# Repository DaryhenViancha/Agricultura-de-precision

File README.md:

# Control de Biosistemas
Proyecto de Sistemas Embebidos 2021-2.    
Para la documentación del proyecto revisar la wiki.

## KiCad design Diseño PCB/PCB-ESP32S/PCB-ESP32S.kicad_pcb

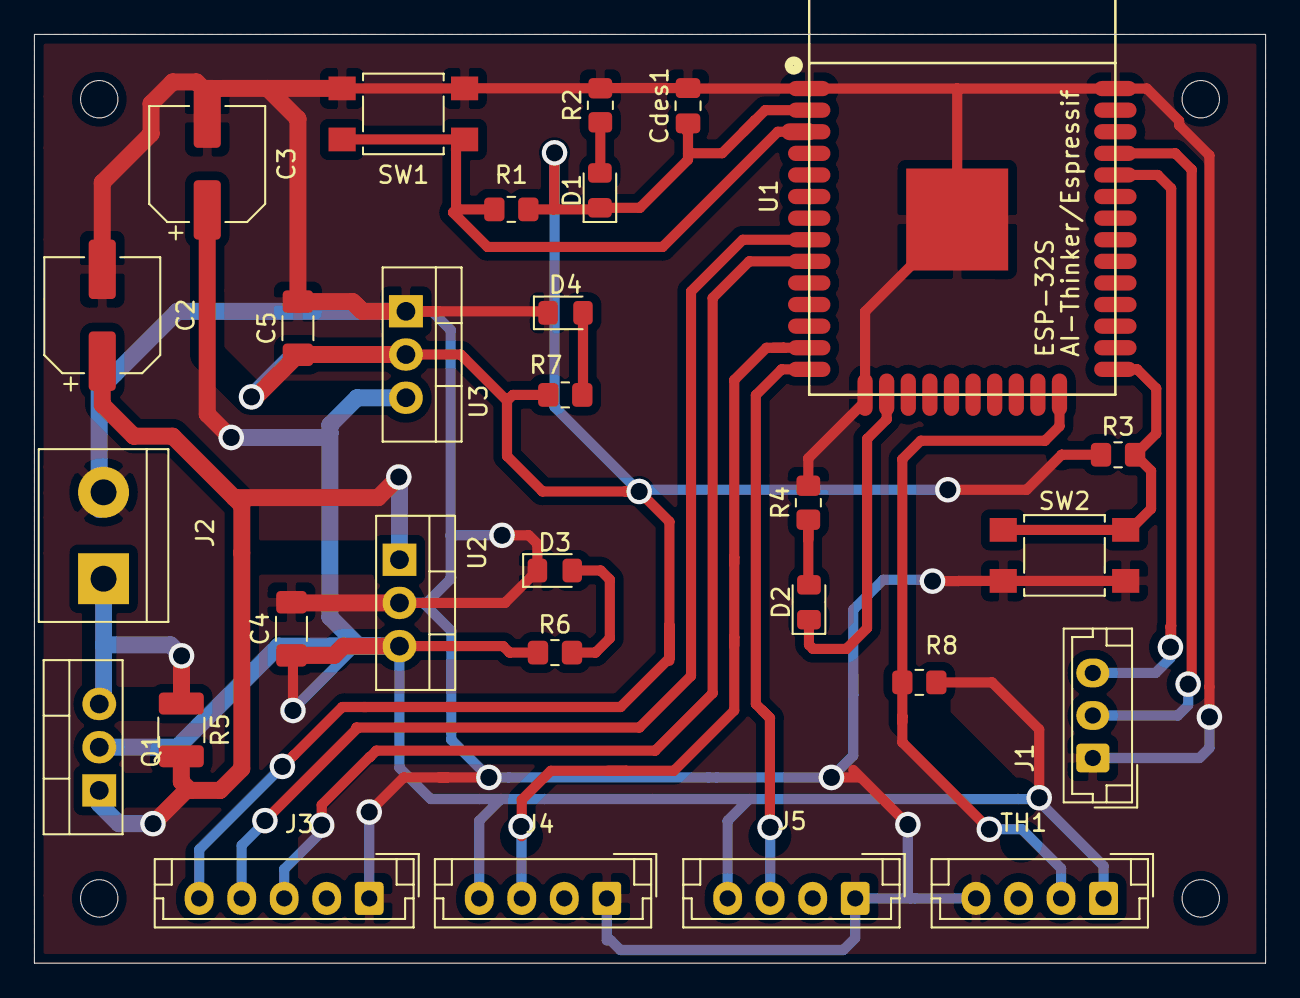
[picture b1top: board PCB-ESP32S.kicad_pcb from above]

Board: 2 copper layers, 72.4 x 54.6 mm, 29 parts (0 on the bottom side), 19 nets.

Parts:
C2, C3: 100u; CP_Elec_6.3x5.8
C4, C5: 10u; C_1206_3216Metric_Pad1.33x1.80mm_HandSolder
Cdes1: 100n; C_0805_2012Metric_Pad1.18x1.45mm_HandSolder
D1, D2, D3, D4: LED; LED_0805_2012Metric_Pad1.15x1.40mm_HandSolder
J1: Screw_Terminal_01x03; JST_EH_B3B-EH-A_1x03_P2.50mm_Vertical
J2: Screw_Terminal_01x02; TerminalBlock_bornier-2_P5.08mm
J3: Conn_01x04; JST_EH_B5B-EH-A_1x05_P2.50mm_Vertical
J4, J5: Conn_01x04_Male; JST_EH_B4B-EH-A_1x04_P2.50mm_Vertical
Q1: TIP42C; TO-220-3_Vertical
R1, R3: 12K; R_0805_2012Metric_Pad1.20x1.40mm_HandSolder
R2, R4: 220; R_0805_2012Metric_Pad1.20x1.40mm_HandSolder
R5: 2; R_1210_3225Metric_Pad1.30x2.65mm_HandSolder
R6: 680; R_0805_2012Metric_Pad1.20x1.40mm_HandSolder
R7: 470; R_0805_2012Metric_Pad1.20x1.40mm_HandSolder
R8: 1k; R_0805_2012Metric_Pad1.20x1.40mm_HandSolder
SW1: SW_DIP_x02; SW_SPST_TL3305A
SW2: SW_DIP_x01; SW_SPST_TL3305A
TH1: DHT22_Temperature_Humidity; JST_EH_B4B-EH-A_1x04_P2.50mm_Vertical
U1: ESP-32S
U2: LM7805_TO220; TO-220-3_Vertical
U3: LM1117-3.3; TO-220-3_Vertical

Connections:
+3V3: C5.1, Cdes1.1, D1.1, J3.5, R1.1, R3.1, R7.1, U1.2, U3.2
+5V: C3.1, C4.1, J4.4, J5.4, Q1.2, R6.1, R8.1, TH1.1, U2.3, U3.3
/Sheet61A8C81E/12v: J2.1, Q1.3, R5.1
GND: C2.2, C3.2, C4.2, C5.2, Cdes1.2, D3.1, D4.1, J1.1, J2.2, J3.1, J4.1, J5.1, R2.2, R4.2, SW1.1, SW2.2, TH1.4, U1.1, U1.15, U1.38, U1.39, U2.2, U3.1
IO2: R8.2, TH1.2, U1.24
IO12: J5.3, U1.14
IO14: J4.3, U1.13
IO32: J3.4, U1.8
IO33: J3.3, U1.9
unnamed: C2.1, Q1.1, R5.2, U2.1
unnamed: D1.2, R2.1
unnamed: D2.1, U1.16
unnamed: D2.2, R4.1
unnamed: D3.2, R6.2
unnamed: D4.2, R7.2
unnamed: J1.2, U1.35
unnamed: J1.3, U1.34
unnamed: R1.2, SW1.2, U1.3
unnamed: R3.2, SW2.1, U1.25

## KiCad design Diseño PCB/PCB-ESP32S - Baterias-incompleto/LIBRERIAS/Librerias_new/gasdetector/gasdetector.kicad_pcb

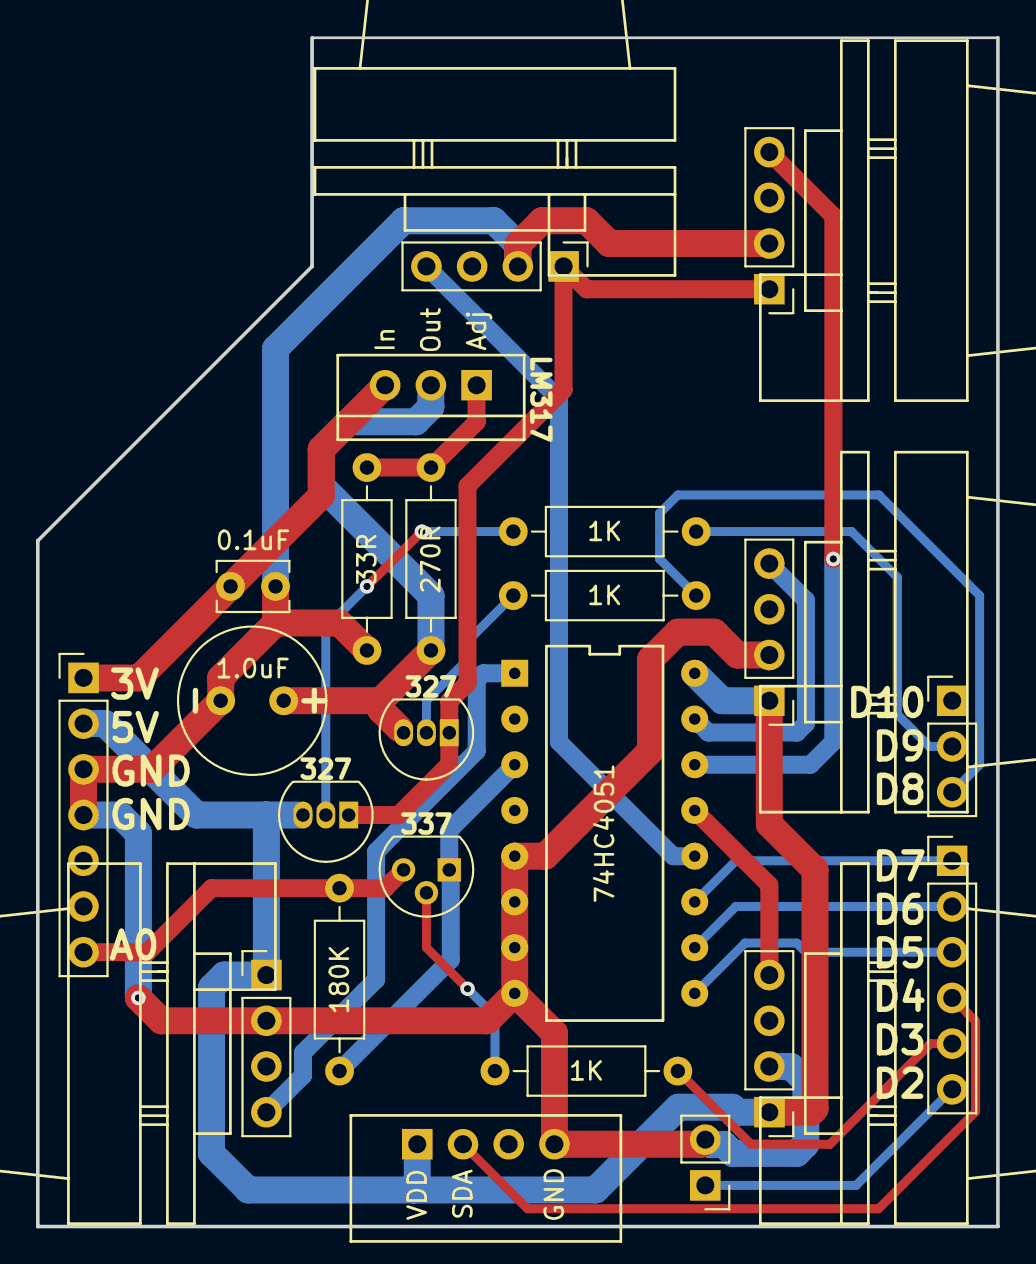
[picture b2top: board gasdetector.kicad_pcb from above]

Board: 2 copper layers, 53.3 x 66.0 mm, 23 parts (0 on the bottom side), 24 nets.

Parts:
C1: 1.0uF; C_Radial_D8.0mm_H7.0mm_P3.50mm
C2: 0.1uF; C_Disc_D3.8mm_W2.6mm_P2.50mm
J1: Conn_01x07_Male; PinHeader_1x07_P2.54mm_Vertical
J2: SetupMode; PinHeader_1x02_P2.54mm_Vertical
J3: D8-D10; PinHeader_1x03_P2.54mm_Vertical
J4: D2-D7; PinHeader_1x06_P2.54mm_Vertical
Q1, Q3: BC327; TO-92_Inline
Q2: BC337; TO-92
R1, R5, R6: 1K; R_Axial_DIN0207_L6.3mm_D2.5mm_P10.16mm_Horizontal
R2, R3: R; R_Axial_DIN0207_L6.3mm_D2.5mm_P10.16mm_Horizontal
R4: 180K; R_Axial_DIN0207_L6.3mm_D2.5mm_P10.16mm_Horizontal
S1: MQ-2; MQ-x
S2: MQ-7; MQ-x
S3: MQ-8; MQ-x
S4: MQ-9; MQ-x
S5: MQ-135; MQ-x
U1: 74HC4051; 74HC4051N
U2: DHT11; AM2302
U3: LM317_3PinPackage; LM317

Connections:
+3V3: C2.2, J1.1, U3.3
+5V: J1.2, Q3.3, S1.1, S3.1, S5.1, U1.16, U2.1
GND: C1.1, C2.1, J1.3, J1.4, J2.2, R3.1, S1.2, S2.2, S3.2, S4.2, S5.2, U1.5, U1.6, U1.7, U1.8, U2.4
unnamed: C1.2, Q1.3, R2.2, U3.2
unnamed: J1.7, Q2.3, R4.2
unnamed: J2.1, J4.6
unnamed: J3.2, R6.2
unnamed: J3.3, R1.2
unnamed: J4.1, U1.11
unnamed: J4.2, U1.10
unnamed: J4.3, U1.9
unnamed: J4.4, U2.2
unnamed: J4.5, R5.1
unnamed: Q1.1, Q3.1, S2.1, S4.1
unnamed: Q1.2, R1.1
unnamed: Q2.1, R4.1, U1.3
unnamed: Q2.2, R5.2
unnamed: Q3.2, R6.1
unnamed: R2.1, R3.2, U3.1
unnamed: S1.4, U1.13
unnamed: S2.4, U1.14
unnamed: S3.4, U1.15
unnamed: S4.4, U1.12
unnamed: S5.4, U1.1

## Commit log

2021-10-21 mi primer cambi
2021-10-21 mis-cambios
2021-10-21 listones
2021-10-21 vamos
2021-10-21 Proyecto
2021-11-04 Arquitectura
2021-11-04 imagen arquitectura
2021-11-04 Datasheet ESP32-s
2021-11-09 Datasheet y esquematicos
2021-11-23 Librerias
2021-11-23 carpeta
2021-11-23 a carpeta
2021-11-23 modelo snapeda
2021-11-24 Ay we
2021-11-24 Hojas de datos
2021-11-24 Diagramas procesos del proyecto
2021-11-24 añadido
2021-11-24 Johan:Mejor proveedor del mundo mundial
2021-11-24 No era tan bueno ioni
2021-11-24 mq135
2021-11-24 mas esquematicos
2021-11-25 KiCad
2021-11-25 Carlos
2021-11-25 agregando esp32 y pcb v1
2021-11-25 Relé control de motores
2021-11-25 sensores
2021-11-25 DHT22PCB
2021-11-25 DTH22
2021-11-25 variables globales
2021-11-25 borrando
2021-11-25 borrando2
2021-11-25 agregando esp32s
2021-11-25 actualizando dibujo
2021-11-25 beta sensores yl100 & mq135
2021-11-30 Modulo Relé
2021-11-30 Actualización
2021-11-30 Actualizo
2021-12-02 Actualización modulo Relé
2021-12-02 Humedad y luz
2021-12-02 Actualización Relé
2021-12-02 actualizacion alimentacion
2021-12-02 Actualización footprints
2021-12-02 footprint sensores mq135 y yl100
2021-12-02 foot print mq135 y yl100
2021-12-16 esp-32 actualizacion
2021-12-16 Actualización2
2021-12-18 Baterías-actualización
2021-12-19 verificacion componentes
2021-12-19 LuzSens-actualización
2022-01-12 Pines sensores
2022-01-12 Baterías
2022-01-13 separacion
2022-01-13 reles
2022-01-13 pcb1
2022-01-14 PCB2
2022-01-14 PCB reles
2022-01-14 alimentacion
2022-01-14 sensores y cto esp32
2022-01-14 PCBs ok
2022-01-17 pcv v2
2022-01-18 PCB reles - GND plano
2022-01-18 mejoras pcb1
2022-01-20 dos pcb finalizadas
2022-01-20 archivos bom y gerber para manufactura
2022-01-20 edicion true hole
2022-01-20 PCB relés, te lo juro por Dieguito Maradona :''v
2022-01-20 archivos bom y gerber para manufactura - mod
2022-01-24 Cotizaciones
2022-01-24 Vamos a alokarnoz
2022-01-24 Cotizaciones2
2022-01-25 imagenes_wiki
2022-01-25 imagenes_diseño en kicad
2022-01-30 pcb elaboradas
2022-01-30 primer cambio super problema
2022-01-30 PCB caca super caca2
2022-01-31 logos distribuidores
2022-01-31 logos distribuidores 2
2022-02-07 pcb con elementos soldados
2022-02-07 pcb con elementos soldados2
2022-02-09 prog_sensores
2022-02-09 org carpetas
2022-02-09 Programas
2022-02-09 BH1750
2022-02-10 prog 2
2022-02-10 Add files via upload
    .
2022-02-10 prog 3
